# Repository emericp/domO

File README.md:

# domO
home automation base on RPI, OpenHAB, MQTT, Arduino, Ethernet Shield, NRF24L01+, etc...

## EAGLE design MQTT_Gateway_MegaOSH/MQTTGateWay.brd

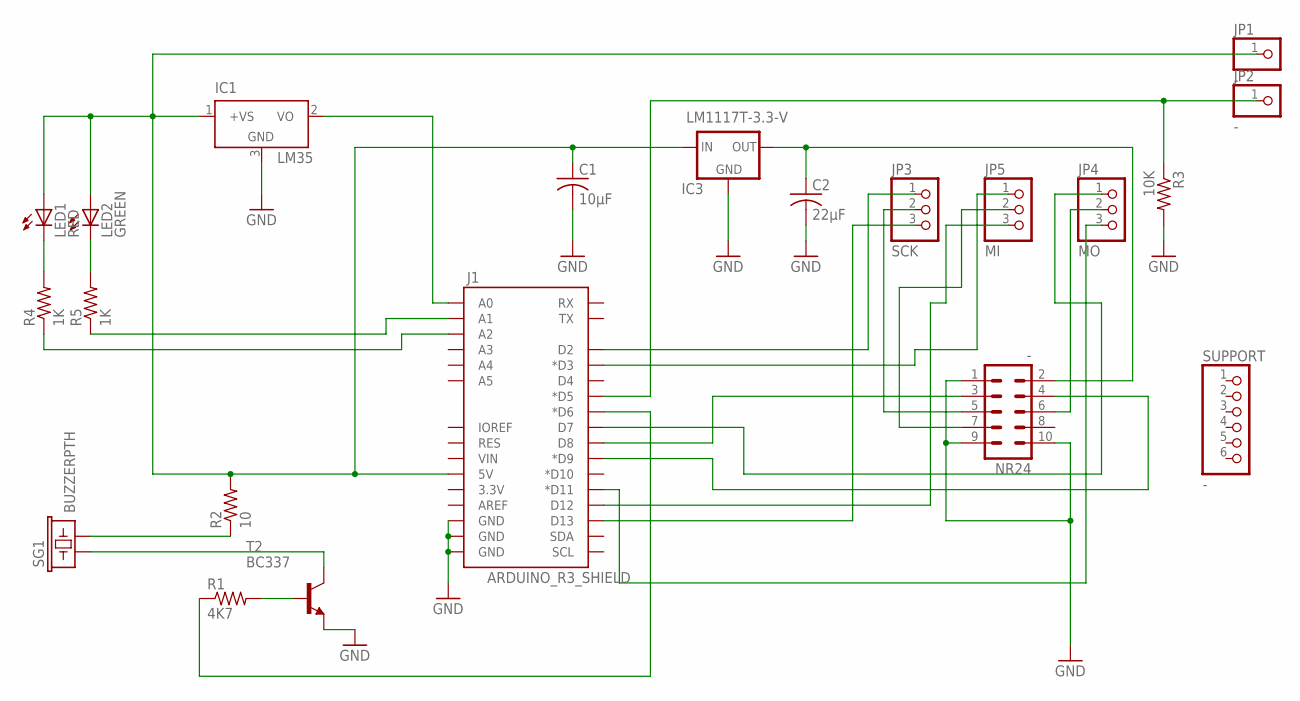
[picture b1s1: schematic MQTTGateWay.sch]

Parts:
C1: 10µF; C025-024X044
C2: 22µF; C025-024X044
IC1: LM35; TO92
IC3: LM1117T-3.3-V; TO220V
J1: ARDUINO_R3_SHIELD; UNO_R3_SHIELD
JP1, JP2: -; 1X01
JP3: SCK; 1X03
JP4: MO; 1X03
JP5: MI; 1X03
LED1: RED; LED3MM
LED2: GREEN; LED3MM
NR24: -; MA05-2
R1: 4K7; 0207/10
R2: 10; 0207/10
R3: 10K; 0207/10
R4, R5: 1K; 0207/10
SG1: BUZZERPTH; BUZZER-12MM
SUPPORT: -; 1X06
T2: BC337; TO92

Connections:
GND: C1.2, C2.2, IC1.3 (GND), IC3.1 (GND), J1.GND@0 (GND), J1.GND@1 (GND), J1.GND@2 (GND), NR24.1, NR24.9, NR24.10, R3.2, T2.1 (E)
MISO: J1.D3 (*D3), JP5.1
MOSI: J1.D7, JP4.1
unnamed: J1.D5 (*D5), JP2.1, R3.1
unnamed: R1.2, T2.2 (B)
unnamed: C2.1, IC3.2 (OUT), NR24.2
unnamed: J1.D8, NR24.3
unnamed: J1.D9 (*D9), NR24.4
unnamed: JP4.2, NR24.6
unnamed: JP5.2, NR24.7
unnamed: J1.D13, JP3.3
unnamed: J1.D12, JP5.3
unnamed: J1.D11 (*D11), JP4.3
unnamed: R2.1, SG1.- (2)
unnamed: SG1.+ (1), T2.3 (C)
unnamed: J1.D6 (*D6), R1.1
unnamed: LED1.K (C), R4.2
unnamed: IC1.2 (VO), J1.A0
unnamed: LED2.K (C), R5.2
unnamed: J1.A1, R5.1
unnamed: J1.A2, R4.1
SCK: JP3.2, NR24.5
SSCK: J1.D2, JP3.1
VCC: C1.1, IC1.1 (+VS), IC3.3 (IN), J1.5V, JP1.1, LED1.A, LED2.A, R2.2

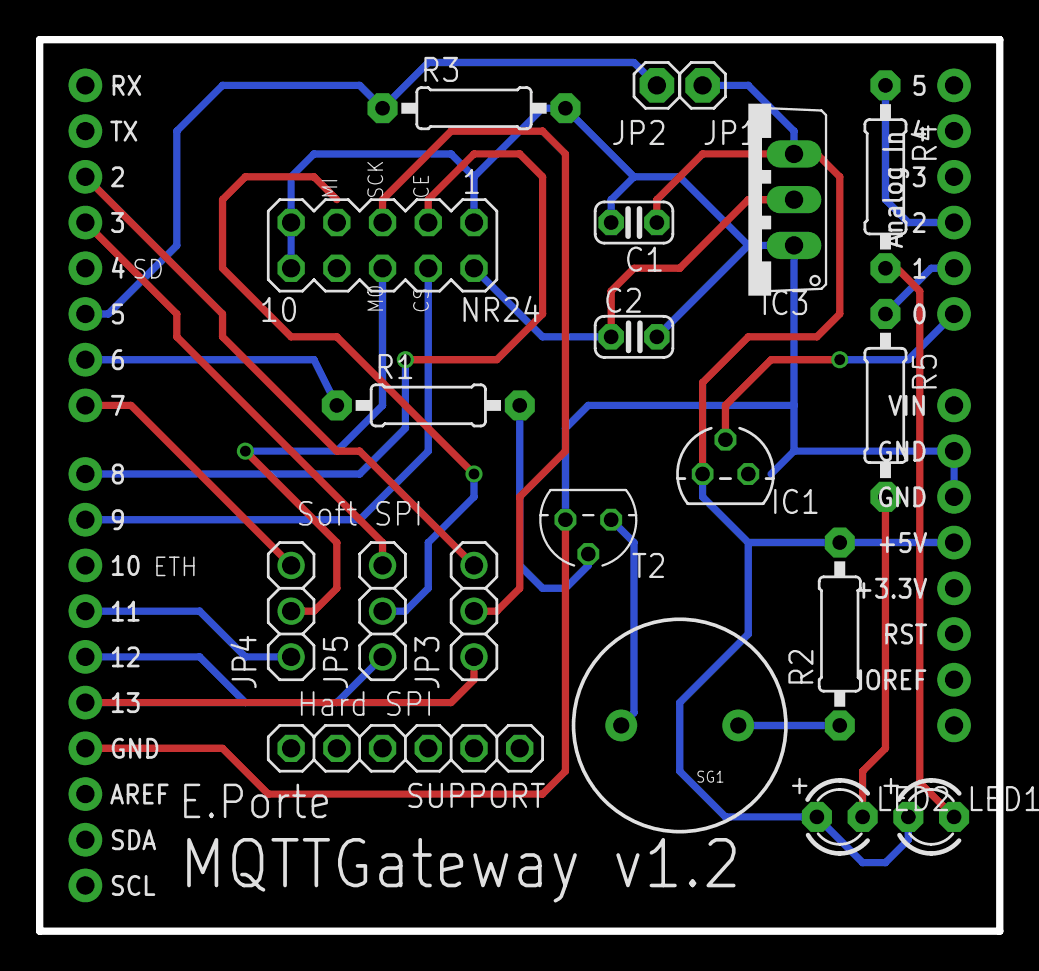
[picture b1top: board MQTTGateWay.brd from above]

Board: 2 copper layers, 53.3 x 49.5 mm, 21 parts (0 on the bottom side), 24 nets.

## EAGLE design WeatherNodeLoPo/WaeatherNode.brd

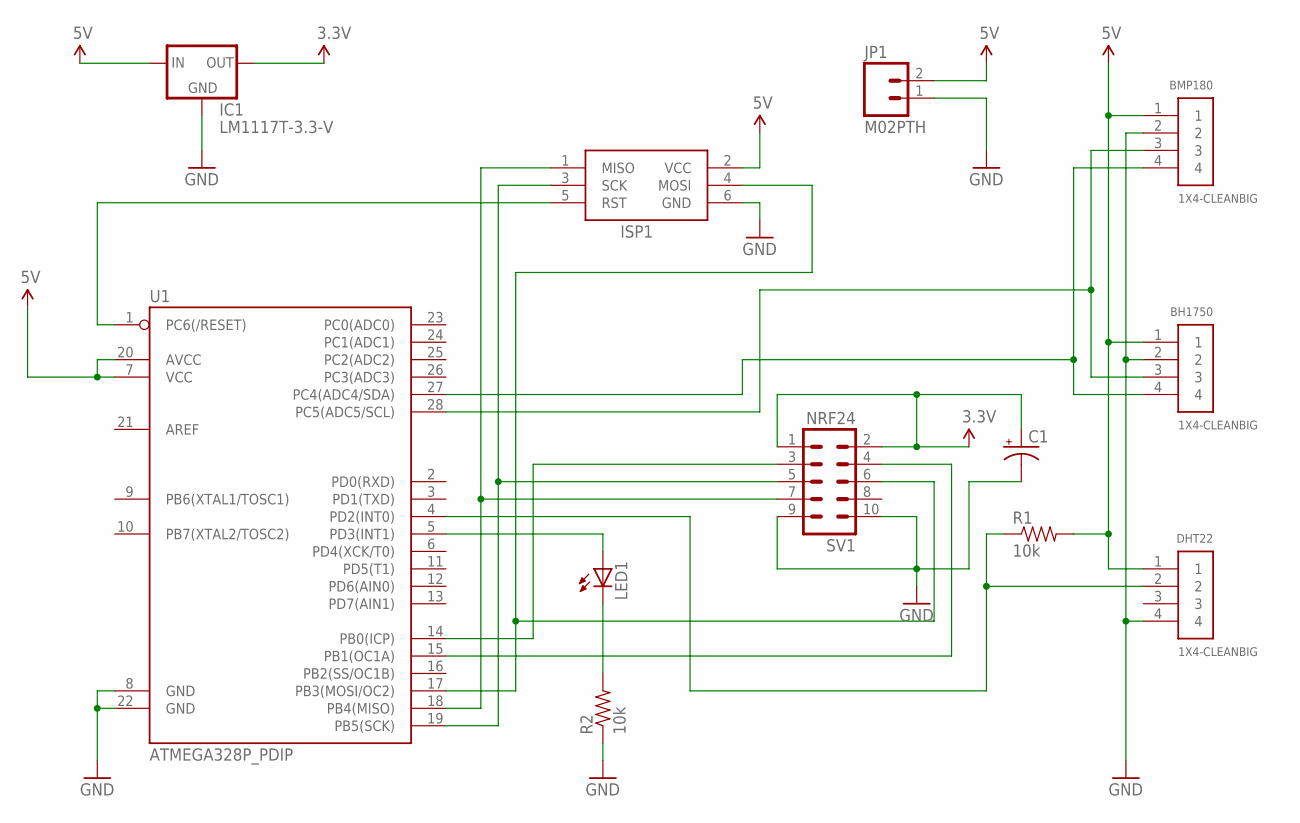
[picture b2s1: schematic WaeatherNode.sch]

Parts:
BH1750: 1X4-CLEANBIG; 1X04-CLEANBIG
BMP180: 1X4-CLEANBIG; 1X04-CLEANBIG
C1: CPOL-USE2.5-7; E2,5-7
DHT22: 1X4-CLEANBIG; 1X04-CLEANBIG
IC1: LM1117T-3.3-V; TO220V
ISP1: AVRISP-BOX
JP1: M02PTH; 1X02
LED1: LED3MM
R1, R2: 10k; AXIAL-0.3
SV1: NRF24; MA05-2
U1: ATMEGA328P_PDIP; DIL28-3

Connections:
3.3V: C1.+, IC1.2 (OUT), SV1.1, SV1.2
5V: BH1750.1, BMP180.1, DHT22.1, IC1.3 (IN), ISP1.2 (VCC), JP1.2, R1.P$2 (2), U1.7 (VCC), U1.20 (AVCC)
GND: BH1750.2, BMP180.2, C1.-, DHT22.4, IC1.1 (GND), ISP1.6 (GND), JP1.1, R2.P$1 (1), SV1.9, SV1.10, U1.8 (GND), U1.22 (GND)
unnamed: ISP1.4 (MOSI), SV1.6, U1.17 (PB3(MOSI/OC2))
unnamed: ISP1.5 (RST), U1.1 (PC6(/RESET))
unnamed: ISP1.3 (SCK), SV1.5, U1.19 (PB5(SCK))
unnamed: ISP1.1 (MISO), SV1.7, U1.18 (PB4(MISO))
unnamed: BH1750.4, BMP180.4, U1.27 (PC4(ADC4/SDA))
unnamed: BH1750.3, BMP180.3, U1.28 (PC5(ADC5/SCL))
unnamed: SV1.3, U1.14 (PB0(ICP))
unnamed: SV1.4, U1.15 (PB1(OC1A))
unnamed: DHT22.2, R1.P$1 (1), U1.4 (PD2(INT0))
unnamed: LED1.A, U1.5 (PD3(INT1))
unnamed: LED1.K (C), R2.P$2 (2)

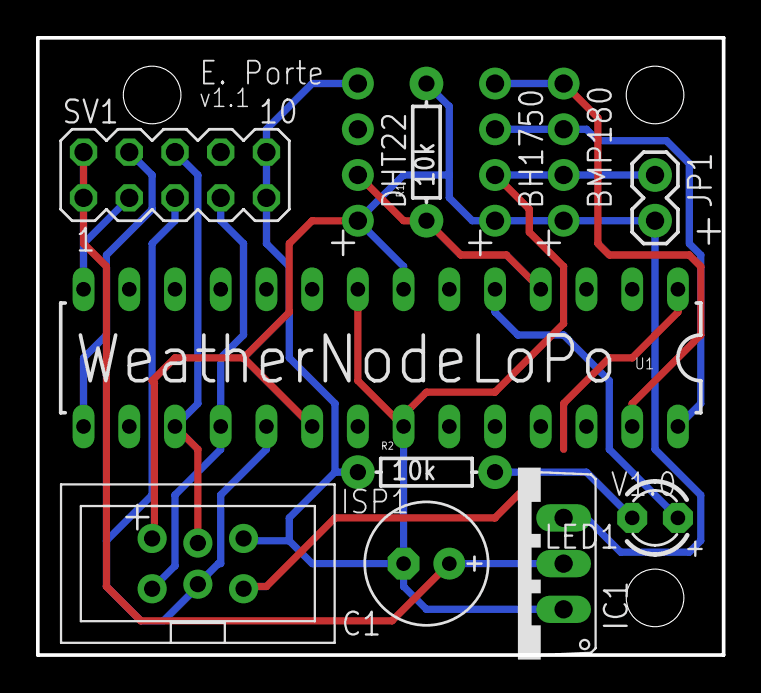
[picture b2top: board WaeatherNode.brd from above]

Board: 2 copper layers, 38.1 x 34.3 mm, 12 parts (0 on the bottom side), 14 nets.

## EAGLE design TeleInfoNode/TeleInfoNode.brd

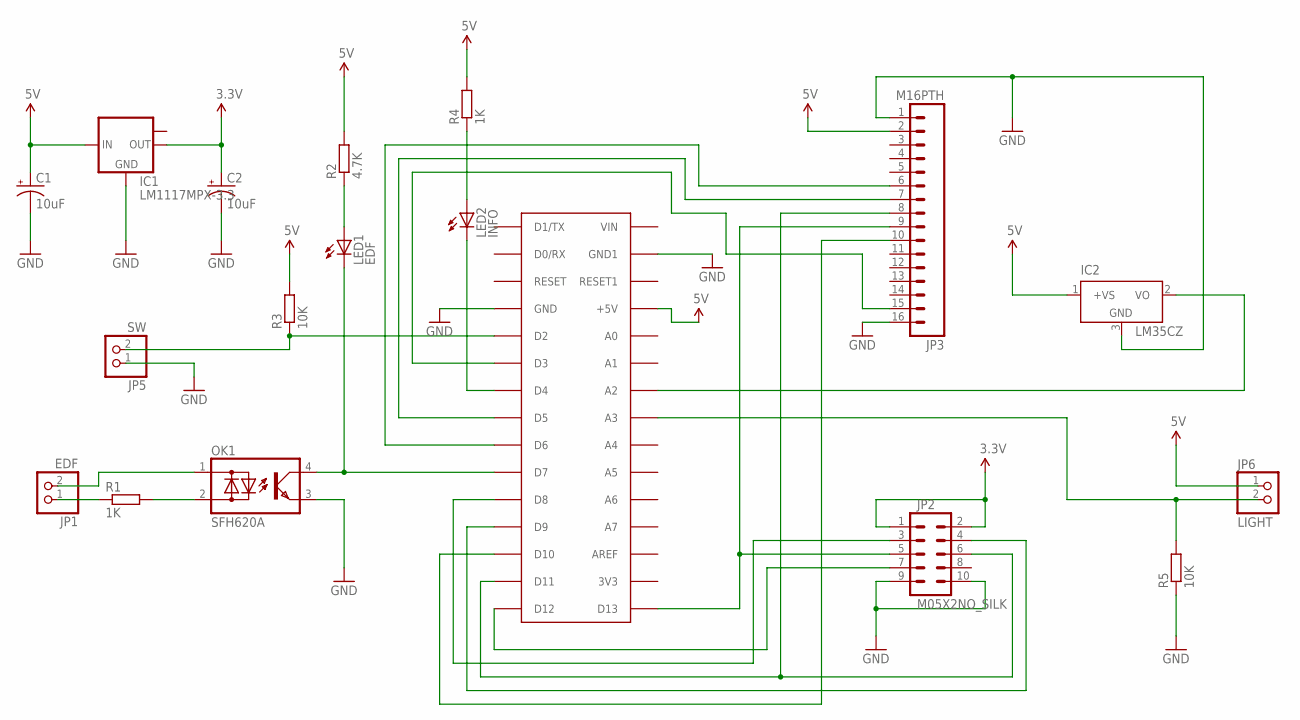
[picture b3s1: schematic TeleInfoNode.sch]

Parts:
C1, C2: 10uF; EIA3216
IC1: LM1117MPX-3.3; SOT223
IC2: LM35CZ; TO92
JP1: EDF; 1X02
JP2: M05X2NO_SILK; 2X5_NOSILK
JP3: M16PTH; 1X16
JP5: SW; 1X02
JP6: LIGHT; 1X02
LED1: EDF; LED3MM
LED2: INFO; LED3MM
OK1: SFH620A; DIL04
R1, R4: 1K; 0204/7
R2: 4.7K; 0204/7
R3, R5: 10K; 0204/7
U$1: ARDUINONANO; PDIP-32

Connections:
3.3V: C2.A (+), IC1.2 (OUT), JP2.1, JP2.2
5V: C1.A (+), IC1.3 (IN), IC2.1 (+VS), JP3.2, JP6.1, R2.2, R3.2, R4.2, U$1.+5V
GND: C1.C (-), C2.C (-), IC1.1 (GND), IC2.3 (GND), JP2.9, JP2.10, JP3.1, JP3.16, JP5.1, OK1.3 (E), R5.1, U$1.GND, U$1.GND1
unnamed: LED1.K (C), OK1.4 (C), U$1.D7
unnamed: LED1.A, R2.1
unnamed: JP1.2, OK1.1 (AC1)
unnamed: JP1.1, R1.1
unnamed: OK1.2 (AC2), R1.2
unnamed: JP2.3, U$1.D8
unnamed: JP2.4, U$1.D9
unnamed: JP2.5, JP3.9, U$1.D13
unnamed: JP2.6, JP3.8, U$1.D11
unnamed: JP2.7, U$1.D12
unnamed: IC2.2 (VO), U$1.A2
unnamed: JP3.10, U$1.D10
unnamed: JP3.6, U$1.D6
unnamed: JP3.7, U$1.D5
unnamed: JP3.15, U$1.D3
unnamed: LED2.A, R4.1
unnamed: LED2.K (C), U$1.D4
unnamed: JP5.2, R3.1, U$1.D2
unnamed: JP6.2, R5.2, U$1.A3

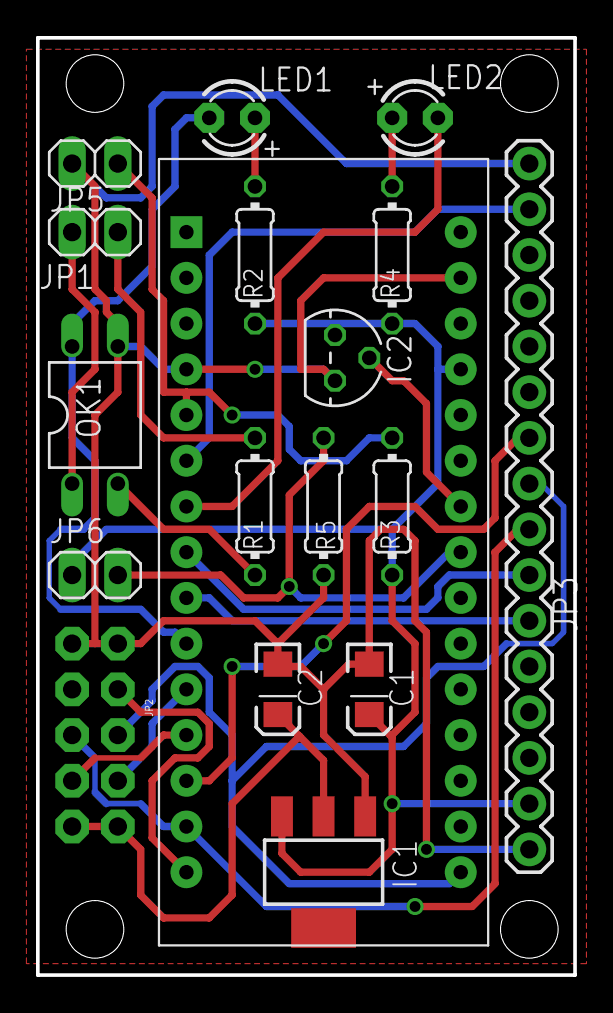
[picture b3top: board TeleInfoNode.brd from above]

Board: 2 copper layers, 29.8 x 52.1 mm, 18 parts (0 on the bottom side), 22 nets.

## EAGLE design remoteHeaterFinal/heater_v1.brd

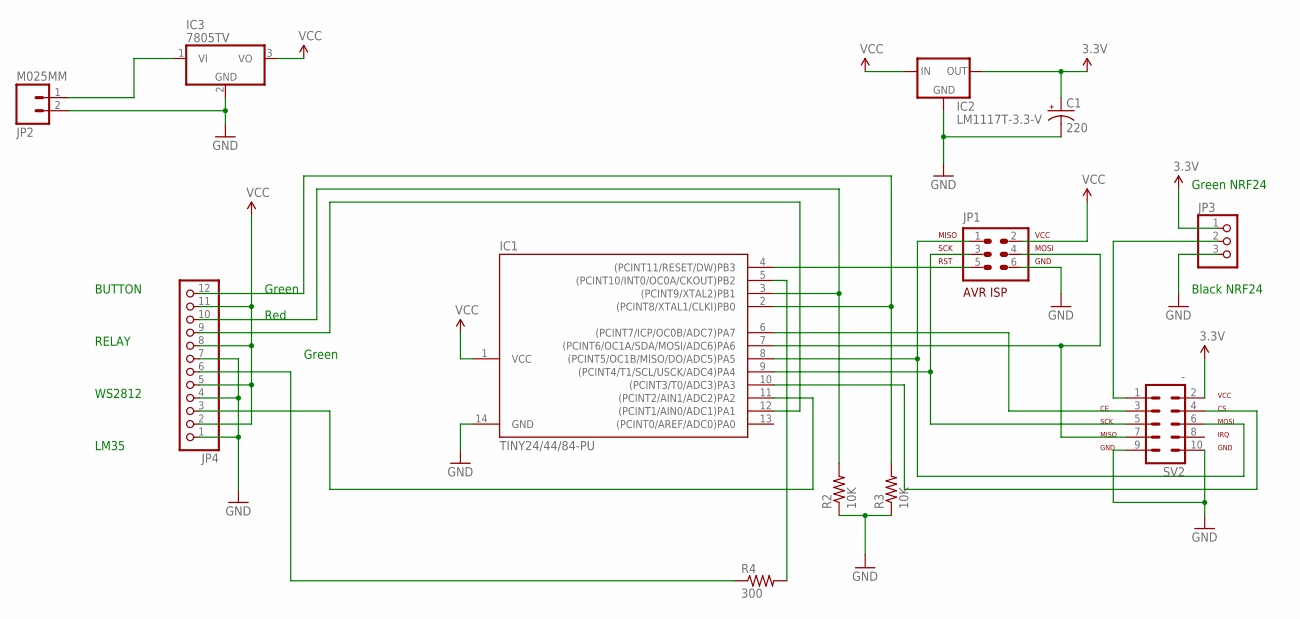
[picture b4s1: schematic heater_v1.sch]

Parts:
C1: 220; E2,5-6
IC1: TINY24/44/84-PU; DIL14
IC2: LM1117T-3.3-V; TO220V
IC3: 7805TV; TO220V
JP1: AVR-ISP-6VERT; AVR-ISP-6
JP2: M025MM; SCREWTERMINAL-5MM-2
JP3: 1X03
JP4: 1X12-CB
R2, R3: 10K; 0204/7
R4: 300; 0204/7
SV2: -; MA05-2

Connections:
3.3V: C1.+, IC2.2 (OUT), JP3.1, SV2.2
GND: C1.-, IC1.14 (GND), IC2.1 (GND), IC3.2 (GND), JP1.6, JP2.2, JP3.3, JP4.1, JP4.4, JP4.7, R2.1, R3.1, SV2.9, SV2.10
unnamed: IC1.5 ((PCINT10/INT0/OC0A/CKOUT)PB2), R4.2
unnamed: IC1.4 ((PCINT11/RESET/DW)PB3), JP1.5
unnamed: IC1.7 ((PCINT6/OC1A/SDA/MOSI/ADC6)PA6), JP1.4, SV2.7
unnamed: IC1.8 ((PCINT5/OC1B/MISO/DO/ADC5)PA5), JP1.1, SV2.6
unnamed: IC1.9 ((PCINT4/T1/SCL/USCK/ADC4)PA4), JP1.3, SV2.5
unnamed: IC1.10 ((PCINT3/T0/ADC3)PA3), SV2.4
unnamed: IC1.6 ((PCINT7/ICP/OC0B/ADC7)PA7), SV2.3
unnamed: IC1.2 ((PCINT8/XTAL1/CLKI)PB0), JP4.12, R3.2
unnamed: IC1.3 ((PCINT9/XTAL2)PB1), JP4.10, R2.2
unnamed: IC1.12 ((PCINT1/AIN0/ADC1)PA1), JP4.9
unnamed: IC1.11 ((PCINT2/AIN1/ADC2)PA2), JP4.3
unnamed: IC3.1 (VI), JP2.1
unnamed: JP4.6, R4.1
unnamed: JP3.2, SV2.1
VCC: IC1.1 (VCC), IC2.3 (IN), IC3.3 (VO), JP1.2, JP4.2, JP4.5, JP4.8, JP4.11

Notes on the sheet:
WS2812
RELAY
BUTTON
Green
Red
VCC
SCK
MISO
GND
MOSI
IRQ
LM35
Black NRF24
Green NRF24

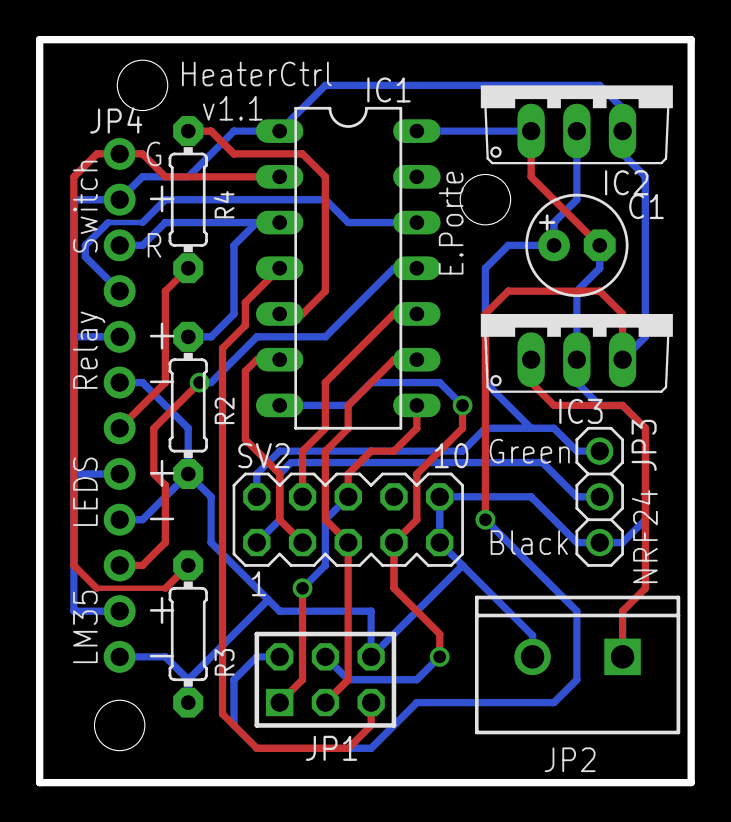
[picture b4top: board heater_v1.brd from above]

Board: 2 copper layers, 36.2 x 41.3 mm, 12 parts (0 on the bottom side), 17 nets.

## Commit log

2015-03-09 MQTT GATEWAY
    Correct unsigned long for lumi value
2015-03-28 New function and bug fixes
    Add logs on SD and watchdog for Gateway, replace DHT22 with DS18B20 and
    HIH6130 on WeatherNode, new items in OpenHAB
2016-01-02 add eagle files
2018-03-19 Xiaomi devices
    add support to xiaomi home automatiom

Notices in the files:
parts and their libraries:
SparkFun-Boards: Licensing: Creative Commons ShareAlike 4.0 International - https://creativecommons.org/licenses/by-sa/4.0
